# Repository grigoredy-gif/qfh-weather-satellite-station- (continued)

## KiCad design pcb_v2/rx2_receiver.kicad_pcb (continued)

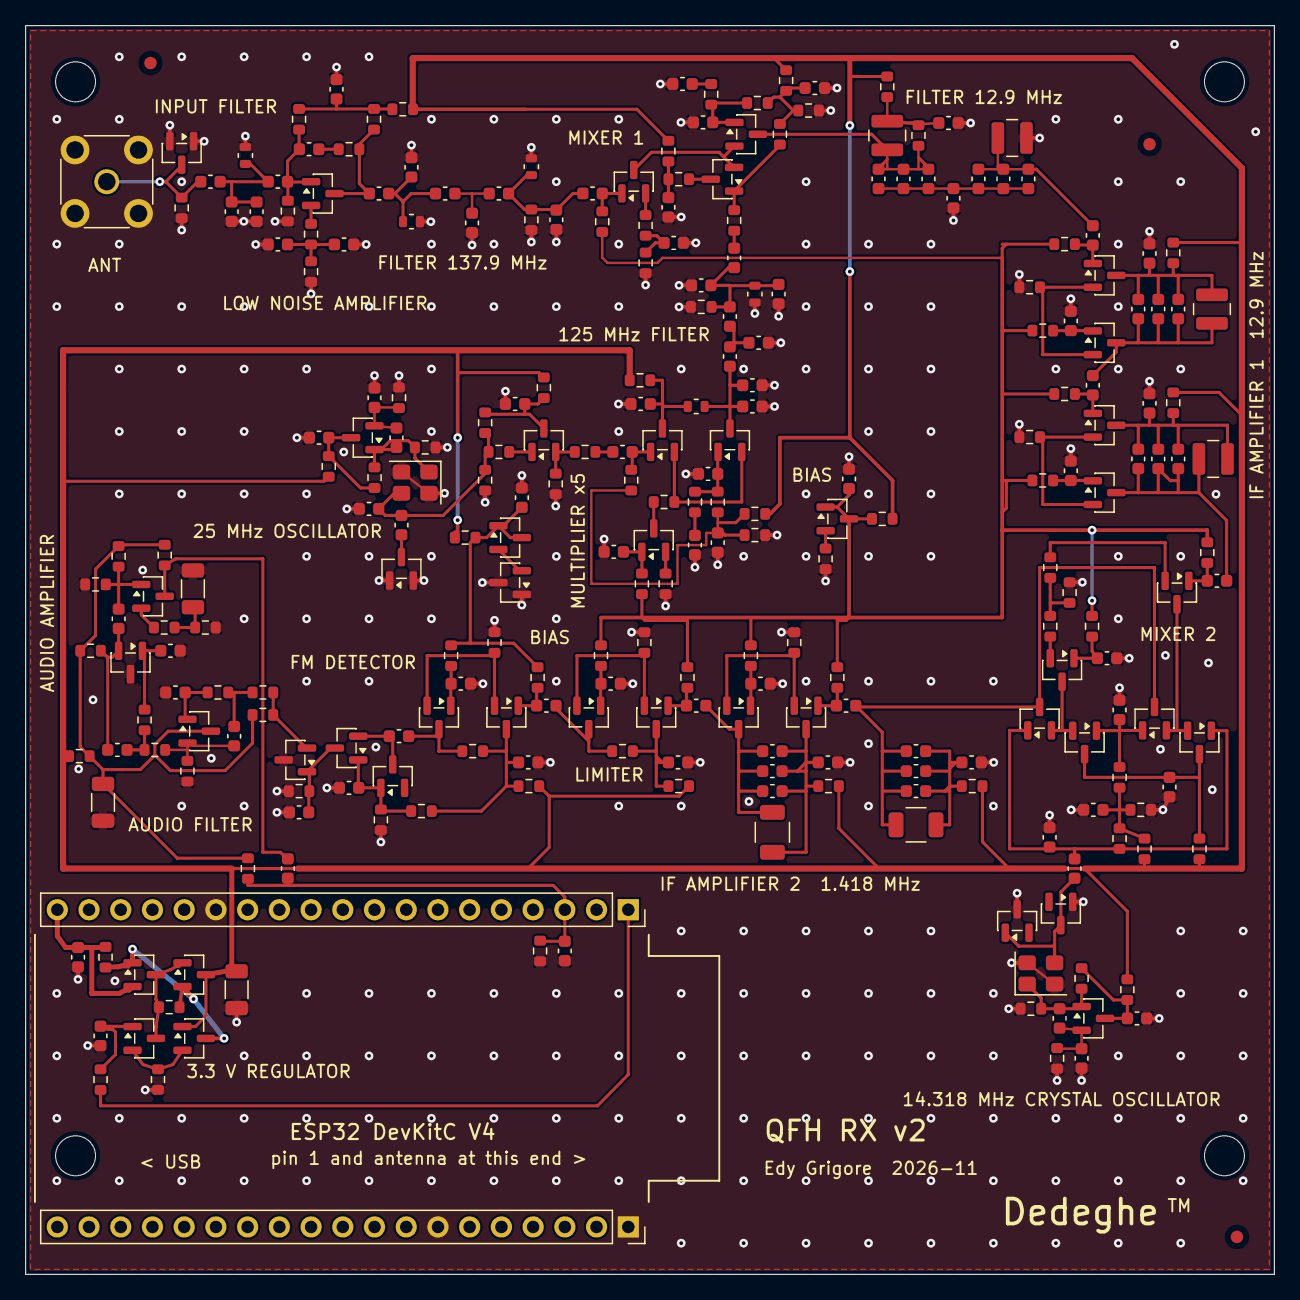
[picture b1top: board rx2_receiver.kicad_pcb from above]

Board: 2 copper layers, 100.0 x 100.0 mm, 273 parts (0 on the bottom side), 117 nets.

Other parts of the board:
FID1, FID2, FID3: Fiducial_1mm_Mask2mm
H1, H2, H3, H4: M3 hole; MountingHole_3.2mm_M3

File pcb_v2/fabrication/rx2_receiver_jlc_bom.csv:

Comment,Designator,Footprint,LCSC Part #
8.2pF,C101,C_0603_1608Metric,C1685
6pF,C102,C_0603_1608Metric,C37474
6.8pF,"C103,C108,C308,C311,C502,C510,C807",C_0603_1608Metric,C1679
1nF,"C104,C105,C106,C304,C402,C404,C405,C507,C512,C701,C804,C809,C903,C905,C909",C_0603_1608Metric,C1588
100nF,"C107,C201,C301,C303,C306,C312,C403,C407,C503,C511,C516,C601,C703,C705,C803,C808,C811,C814",C_0603_1608Metric,C14663
12pF,C109,C_0603_1608Metric,C38523
330pF,"C110,C504",C_0603_1608Metric,C1664
18pF,"C111,C307",C_0603_1608Metric,C1647
47pF,"C202,C501,C505,C816",C_0603_1608Metric,C1671
100pF,"C203,C309,C401,C406,C603,C801,C806",C_0603_1608Metric,C14858
10pF,C204,C_0603_1608Metric,C1634
10nF,"C205,C302,C305,C508,C513,C702,C704,C805,C810,C812,C813",C_0603_1608Metric,C57112
15pF,C310,C_0603_1608Metric,C1644
4.7pF,"C506,C802",C_0603_1608Metric,C1669
33pF,"C509,C514,C605",C_0603_1608Metric,C1663
3pF,C515,C_0603_1608Metric,C46219
68pF,"C602,C604",C_0603_1608Metric,C28262
1uF,"C815,C906,C908",C_0603_1608Metric,C15849
470pF,C817,C_0603_1608Metric,C1620
100uF,"C901,C907,C1003",C_1206_3216Metric,C15008
4.7nF,"C902,C904",C_0603_1608Metric,C53987
10uF,"C1001,C1002,C1101,C1102",C_0603_1608Metric,C19702
BAV99,"D101,D201",SOT-23,C2500
BAS70,"D601,D602,D801",SOT-23,C7502686
68nH,"L101,L102,L103,L301,L302",L_0603_LQW18A,C86135
3.3uH,"L501,L502,L503,L504",L_1008_AHW2520C,C6364740
100uH,"L801,L802",L_1210_NLV32,C295124
2SC3356,"Q101,Q302,Q303,Q304,Q401,Q402,Q403",SOT-23,C28646266
S9018,"Q201,Q301,Q501,Q502,Q503,Q504",SOT-23,C41375130
MMBT3904,"Q601,Q701,Q702,Q703,Q704,Q705,Q706,Q801,Q802,Q803,Q804,Q805,Q806,Q902,Q904,Q1003,Q1004,Q1101,Q1102",SOT-23,C20526
MMBT3906,"Q807,Q901,Q903,Q1001,Q1002,Q1103",SOT-23,C7420354
10k,"R101,R401,R404,R406,R407,R501,R503,R504,R507,R508,R701,R702,R706,R708,R709,R802,R803,R806,R807,R811,R902",R_0603_1608Metric,C25804
1.8k,"R102,R809",R_0603_1608Metric,C4177
1k,"R103,R705",R_0603_1608Metric,C21190
2.2R,R104,R_0603_1608Metric,C22939
33R,"R105,R306",R_0603_1608Metric,C23140
120R,R106,R_0603_1608Metric,C22787
470R,"R107,R204,R812",R_0603_1608Metric,C23179
10R,"R108,R1001",R_0603_1608Metric,C22859
2.2k,"R109,R307,R908,R1004",R_0603_1608Metric,C4190
100R,"R201,R304,R312,R402,R410,R502,R506,R510,R601,R703,R704,R710,R801,R805,R810,R901",R_0603_1608Metric,C22775
22k,"R202,R203,R602,R603,R910",R_0603_1608Metric,C31850
22R,"R301,R316",R_0603_1608Metric,C23345
15k,"R302,R405,R707,R903,R906",R_0603_1608Metric,C22809
33k,R303,R_0603_1608Metric,C4216
390R,"R305,R813",R_0603_1608Metric,C23151
4.7k,"R308,R1103",R_0603_1608Metric,C23162
680R,"R309,R310,R315,R604",R_0603_1608Metric,C23228
47R,"R311,R313,R314,R408,R409,R411,R815,R912",R_0603_1608Metric,C23182
200R,R403,R_0603_1608Metric,C8218
1.2k,"R505,R509,R1003",R_0603_1608Metric,C22765
1.1k,"R804,R814,R1101",R_0603_1608Metric,C22764
560R,R808,R_0603_1608Metric,C23204
1.5k,"R816,R913,R1002",R_0603_1608Metric,C22843
3k,"R817,R911",R_0603_1608Metric,C4211
27k,"R818,R909",R_0603_1608Metric,C22967
5.6k,"R904,R907",R_0603_1608Metric,C23189
2.7k,R905,R_0603_1608Metric,C13167
82k,R914,R_0603_1608Metric,C23254
51k,R915,R_0603_1608Metric,C23196
270R,R1102,R_0603_1608Metric,C22966
25MHz,Y201,Crystal_SMD_3225-4Pin_3.2x2.5mm,C9006
14.31818MHz,Y601,Crystal_SMD_3225-4Pin_3.2x2.5mm,C34748

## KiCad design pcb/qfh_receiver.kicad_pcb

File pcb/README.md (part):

# PCB — discrete 137.9 MHz FM satellite receiver

This is the circuit board for the receiver I simulated in
[`../fm_receiver`](../fm_receiver). The board is built from that simulation:
its schematic was generated from the full-receiver netlist `sim12`, and if the
board and that netlist ever disagree, the netlist wins.

> **Status (November 2026): finished as a design, never ordered or built.**
> The last copper change was on 7 November 2026, and a final check on
> 10 November found nothing that stops the board from working. I did not
> order it: having two boards assembled was quoted at about €140, and by hand
> it means winding 11 coils and aligning 11 trimmers. Its successor,
> [version 2](../pcb_v2), is designed so that JLCPCB can assemble all of it; it
> was ordered on 16 November 2026.
> The comparison is in [the main README](../README.md#from-version-1-to-version-2).

*3D picture of the version 1 board, made by KiCad from the board file (not a photo).*

## The board at a glance

| | |
|---|---|
| Size | 210 × 75 mm, 2 layers, FR4 1.6 mm |
| Parts | 205, all on the top side, all SMD except the 11 hand-wound coils, the antenna SMA, the test SMA and the two ESP32 socket strips |
| Assembly | planned by hand: bare boards from JLCPCB, parts from LCSC (JLC assembly was quoted at about €140 for two boards). Not ordered |
| Bottom layer | one ground plane |
| Controller | ESP32-DevKitC V4 on a socket (its ADC digitizes the audio) |
| Supply | the DevKitC's 5V pin (really about 4.6 V), about 41 mA |
| Checks | KiCad DRC clean at a 0.254 mm clearance floor; schematic and board match pad for pad |

*The final version 1 board from above (KiCad 3D picture). The two yellow strips
across the IF strip are the exposed ground lands for the shield fences.*

*The same board on 13 September 2026 (KiCad 3D picture), before the
through-hole transistors, trimmers and capacitors were swapped for SMD
versions so that a factory could place them. The board was 180 mm long then.*

## Floorplan

```
+----------------------------------------------------------------------------------+
| [SMA ant] BPF (2 air coils, | LNA | MIXER | == IF STRIP, 96 dB, straight ======= |
|  plane cutouts) [SMA test]  | SMD | +L7   |  L1 [1] #F1# [2][3] #F2# [4] lim DET |
|-------- via wall ------------------------------------------------------ via wall|
| LO CHAIN: xtal 25MHz | buffer | x5 (2 air coils) -> up into mixer LO port        |
|                      AUDIO chain (2400 Hz, folds freely) <- from detector        |
|                                   supply filter   ESP32 socket [USB over edge] > |
+----------------------------------------------------------------------------------+
#F1#, #F2# = shield fences: exposed ground strips for 15 mm tin-plate walls
L7, L1 = the two toroid tanks of the IF filter; [1]-[4] = the four IF stages
```

The 4.6 V supply comes in from the ESP32 socket at the right-hand end and is
filtered there before it runs left along the board.

The weakest signals (microvolts) start at the left edge and the strongest
(volts) end at the right. The IF strip runs in a straight line with its input
and output at opposite ends, because with 96 dB of gain even a little coupling
from the output back to the input would make it oscillate.

## Layout rules I followed

- **The bottom layer is ground.** Everything is routed on top, except where a
  trace had to cross another: 27 bottom-layer segments, 171 mm in total on 12
  nets. The longest are two `vb2` bias runs (25 and 16 mm) under the IF strip.
  They carry DC and are bypassed at both ends. Each hop is listed and
  justified in the design log.
- **Shielding provisions for free.** Rows of ground vias between the IF stages
  and between the RF and the LO/audio sections, with exposed ground strips so a
  brass shield can be soldered on later if the strip oscillates.
- **Two shield fences across the toroid row.** A stability study (below)
  showed that the real risk is the toroids themselves, which stand on edge in
  one open row. So the board was made 30 mm longer: a 20 mm gap between
  stage 1 and stage 2 and a 10 mm gap between stage 3 and stage 4. Each gap
  has an exposed ground strip with 15 stitching vias, from the top edge down
  to the via wall. A 15 mm tall tin-plate fence soldered onto each one
  separates three groups:
  - the IF filter and stage 1;
  - stages 2–3;
  - stage 4, the limiter and the detector.

  The strongest sources of feedback (stage 4 and the detector) now have to get
  past two fences to reach the IF filter.
- **Tight RF loops.** Every tuned circuit's parts sit right at its coil, and the
  LNA's emitter bypass is within about 5 mm of copper of the transistor. At VHF
  a few nanohenries of track change the tuning and the gain.
- **A real 50 ohm antenna input.** The SMA feeds the filter through a 1.5 mm
  coplanar line with ground on both sides.
- **Decoupling everywhere.** Every IF stage has its own 100 nF capacitors on its
  supply and on its cascode bias, fed through its own 47 ohm resistor, so the
  stages cannot talk to each other through the supply. The mixer tank L7 has
  its own 10 ohm + 100 nF feed for the same reason.
- **Test points for bring-up.** A second SMA (J2) with a 0 ohm link R65 at the
  filter→LNA seam (remove R65 and J1→J2 is the band-pass filter alone, ready
  for a VNA), an injection pad TP1 at the first IF stage, and a monitor pad
  TP2 on the audio.
- **No parts on the back and no mounting holes**, both on purpose.

The toroids (T37-6, 27 turns) and the air coils (5 mm diameter) use my own
footprints in `qfh_receiver.pretty`. The air-coil footprint keeps copper away
from under the coil, because a ground plane there would kill its Q.

**Winding rule for the toroids: return-wind them.** A winding that advances once
around the core also behaves like one big single turn, and that turn leaks a
magnetic field (the "one-turn effect"). After the last turn, lay the wire back
around the outside of the core to where the winding started, and only then go
to the pin. That cancels most of the leak. It is required on L4, L6 and L5 (the
high-level end of the strip) and costs nothing on the others, so I do it on all
seven.

**Winding rule for the two link windings (L7 and L1): put the 2 turns at the
cold end**, next to pad 1, and ground the link loop with a short wire from L1
pad 5 to L1 pad 1 (about 5 mm). The loop is otherwise floating, and a link
wound over the hot end of a tank has 0.5–1 pF to it. Through the loop that is
0.25–0.5 pF from one tank to the other, next to the 0.77 pF (0.011 × 70 pF)
that the whole designed coupling amounts to. At the cold end and grounded,
that stray path is gone and L13 alone sets the coupling.

**Winding rule for the air coils (L8–L11): spread the turns to a set length.**
Wind them from 0.8 mm wire on a 5 mm former, then pull the turns apart evenly.
The length sets the inductance (Wheeler's formula, good to about ±10 %; a coil
also springs open a little when it comes off the former):

| Coil | Turns | Length | Inductance |
|---|---|---|---|
| L8, L10 (band-pass filter) | 5 | about 7 mm | about 86 nH (82 nH at 7.5 mm) |
| L9, L11 (×5 and LO tanks) | 7 | about 8.2 mm | about 150 nH |

Wound tight, turn against turn, they would be about 120 nH and 190 nH, which
is more than the 4 pF trimmers can pull in. The band-pass coils are a little
short on purpose. Their trimmers are expected near 5 pF of 6 pF: in the
simulation with the board's parasitics, a coil 10 % low needs 6.6 pF, which
the trimmer does not have, and a coil 10 % high needs 4.0 pF, the middle of
its range. At 7 mm the legs also drop straight into the pads.

## How I checked it

KiCad's design-rule check is clean at a 0.254 mm clearance floor. The
schematic was generated from the simulation netlist and compared with the board
pad by pad (436 connections, no differences; the 33 unused ESP32 pins carry
no-connect flags). Every part has a stocked LCSC part number for JLCPCB
assembly. I also had the board reviewed by independent AI review passes, which
is how several of the issues below were found. The last full one, on
6 November 2026, re-ran the simulations against the board as built and checked
it from seven angles (simulation, schematic, RF layout, IF stability, power,
manufacturing, requirements). A final read-only check on 10 November moved no
copper and found nothing that stops the board from working.

## Issues found and fixed

- **Two TO-92 transistor types had base and emitter swapped** because a
  generic symbol used the wrong pin order. Lesson: check each footprint's pinout
  against the datasheet, not against the symbol library.
- **The ESP32 socket would not have powered anything.** The 5 V feed landed on
  a GPIO pin and the enable pin was grounded. I fixed it after checking the
  DevKitC pinout from several sources and every way the module could be
  plugged in.
- **The "5 V" supply is really 4.6 V**, because the DevKitC puts a Schottky
  diode after USB. I re-centred every bias divider in the simulation for 4.6 V
  instead of accepting lower gain.
- **Some specified trimmers did not exist as real parts.** Together with the
  board's own parasitics this pushed three tuned circuits to the end of their
  trimmer range. I re-split the fixed capacitor and the trimmer in each one so
  the trimmer now lands mid-range.
- **The LNA's emitter bypass capacitor was 20 mm from the transistor.** That
  is about 12 nH, which would have cost 4–5 dB of gain. It is now within 5 mm.
- **The IF strip would probably have oscillated.** From the IF filter to the
  last stage there is about 124 dB of gain. In LTspice, a stray coupling of only
  0.045 fF from the last stage back into the IF filter, or a mutual inductance
  of 1.4 pH between two toroids, is enough to make it oscillate. My estimates
  from the board geometry put the toroid-to-toroid coupling at 1–7 times that.
  The supply decoupling and the PCB traces were fine. The fixes are two fences,
  30 mm of extra distance and the return-wound toroids, with the damping
  resistors as a gain knob on the bench. The details are in the design log.
- **Through-hole parts swapped for SMD versions of the same parts** so the board
  can be machine-assembled: the five audio transistors (now MMBT3904/3906 in
  SOT-23), the five diodes, the crystal and the three electrolytics. SOT-23 has
  a different pin order from TO-92 (B-E-C instead of E-B-C), so the schematic
  symbols changed too. I checked afterwards that every pad still carries the
  same net as before.
- **The full check of 6 November 2026 found six more board problems**, all
  fixed:
  - *The IF filter was over-coupled.* Its two toroids are joined by a link
    winding, and the old rule of thumb for the link (k ≈ (n/N)²) is wrong for a
    low-impedance loop. The real coupling would have been 0.08–0.3 instead of
    0.011. That gives one narrow peak, weak skirts and a spurious passband a few
    MHz higher. Fix: 2-turn links plus a 680 nH inductor (L13) in series in the
    link loop. The simulation gives 209 kHz, single-peaked, −24 dB at ±500 kHz.
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
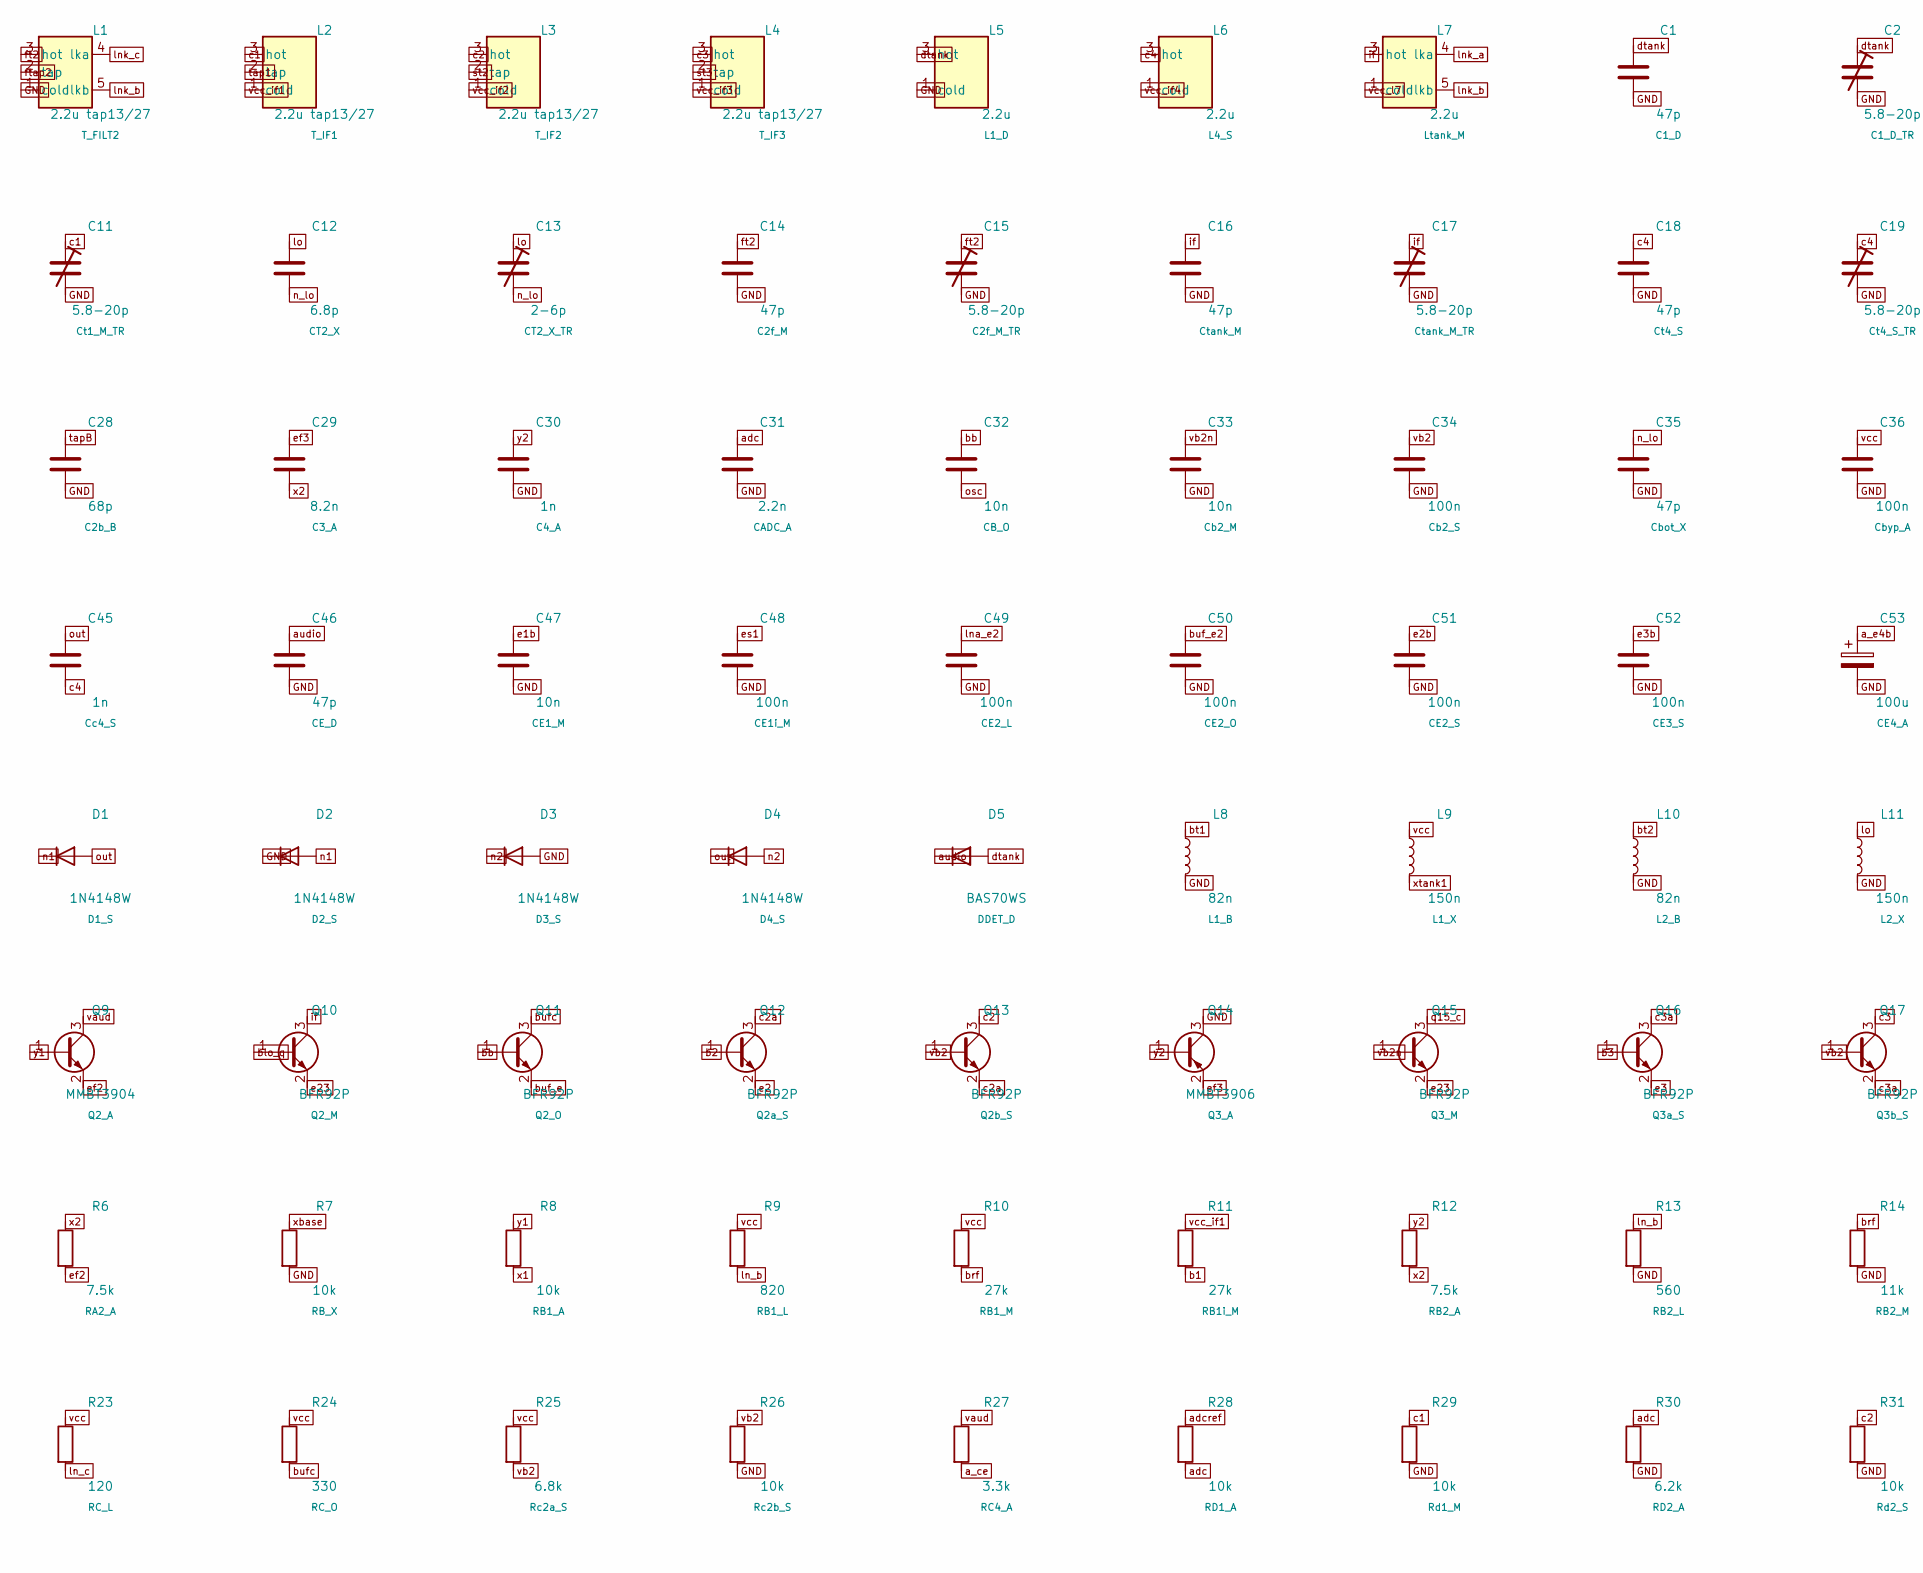
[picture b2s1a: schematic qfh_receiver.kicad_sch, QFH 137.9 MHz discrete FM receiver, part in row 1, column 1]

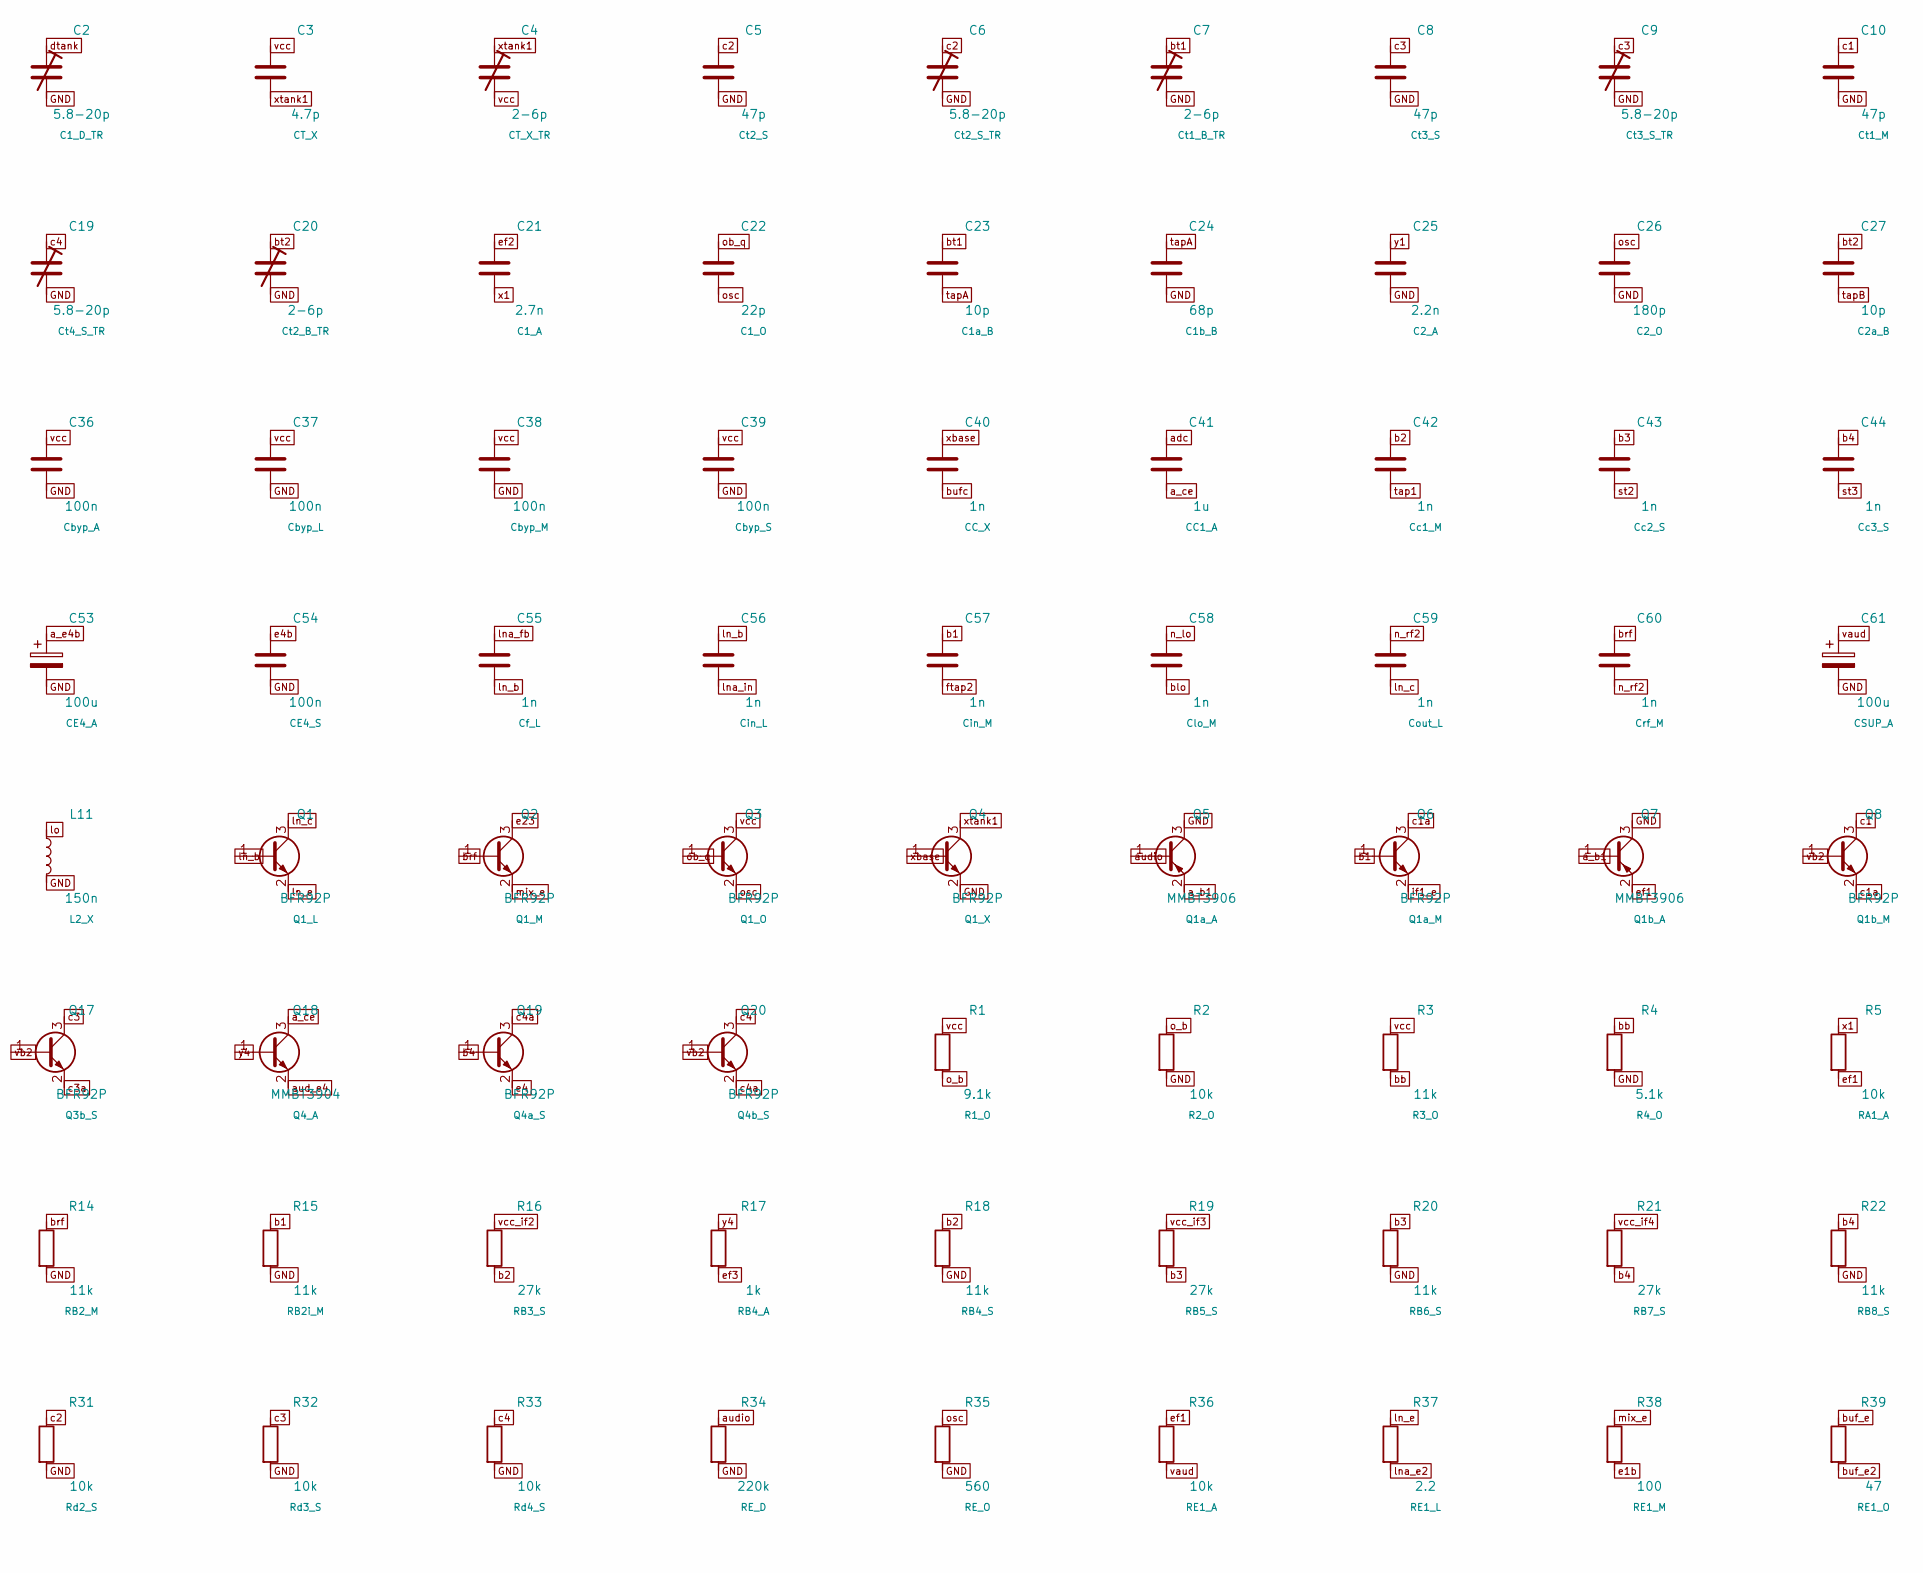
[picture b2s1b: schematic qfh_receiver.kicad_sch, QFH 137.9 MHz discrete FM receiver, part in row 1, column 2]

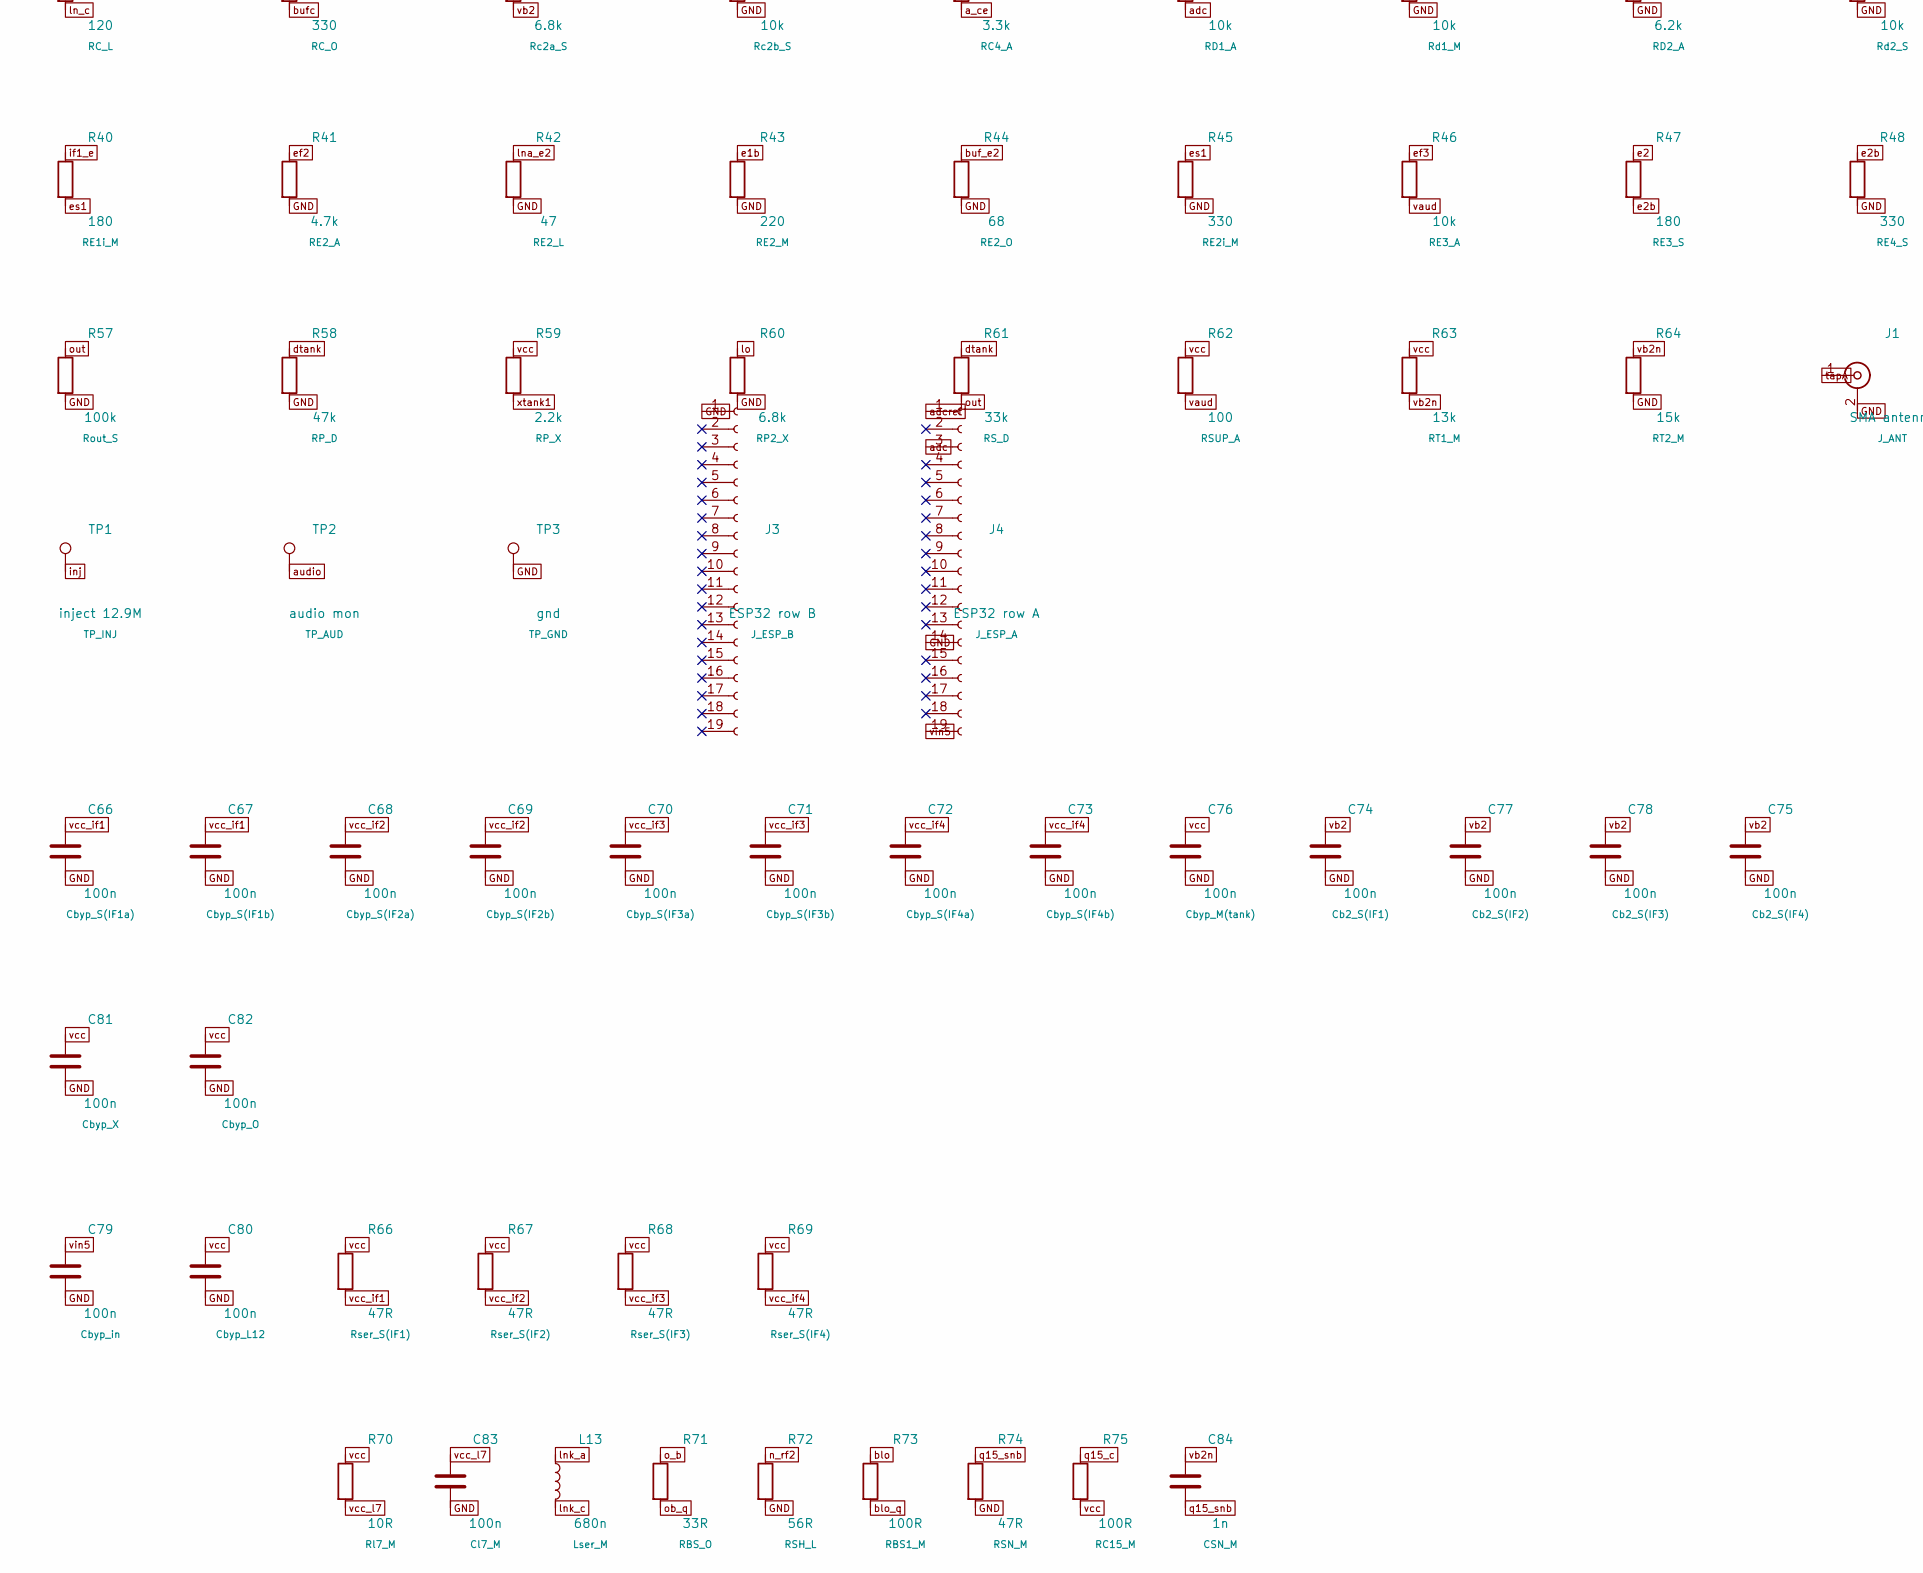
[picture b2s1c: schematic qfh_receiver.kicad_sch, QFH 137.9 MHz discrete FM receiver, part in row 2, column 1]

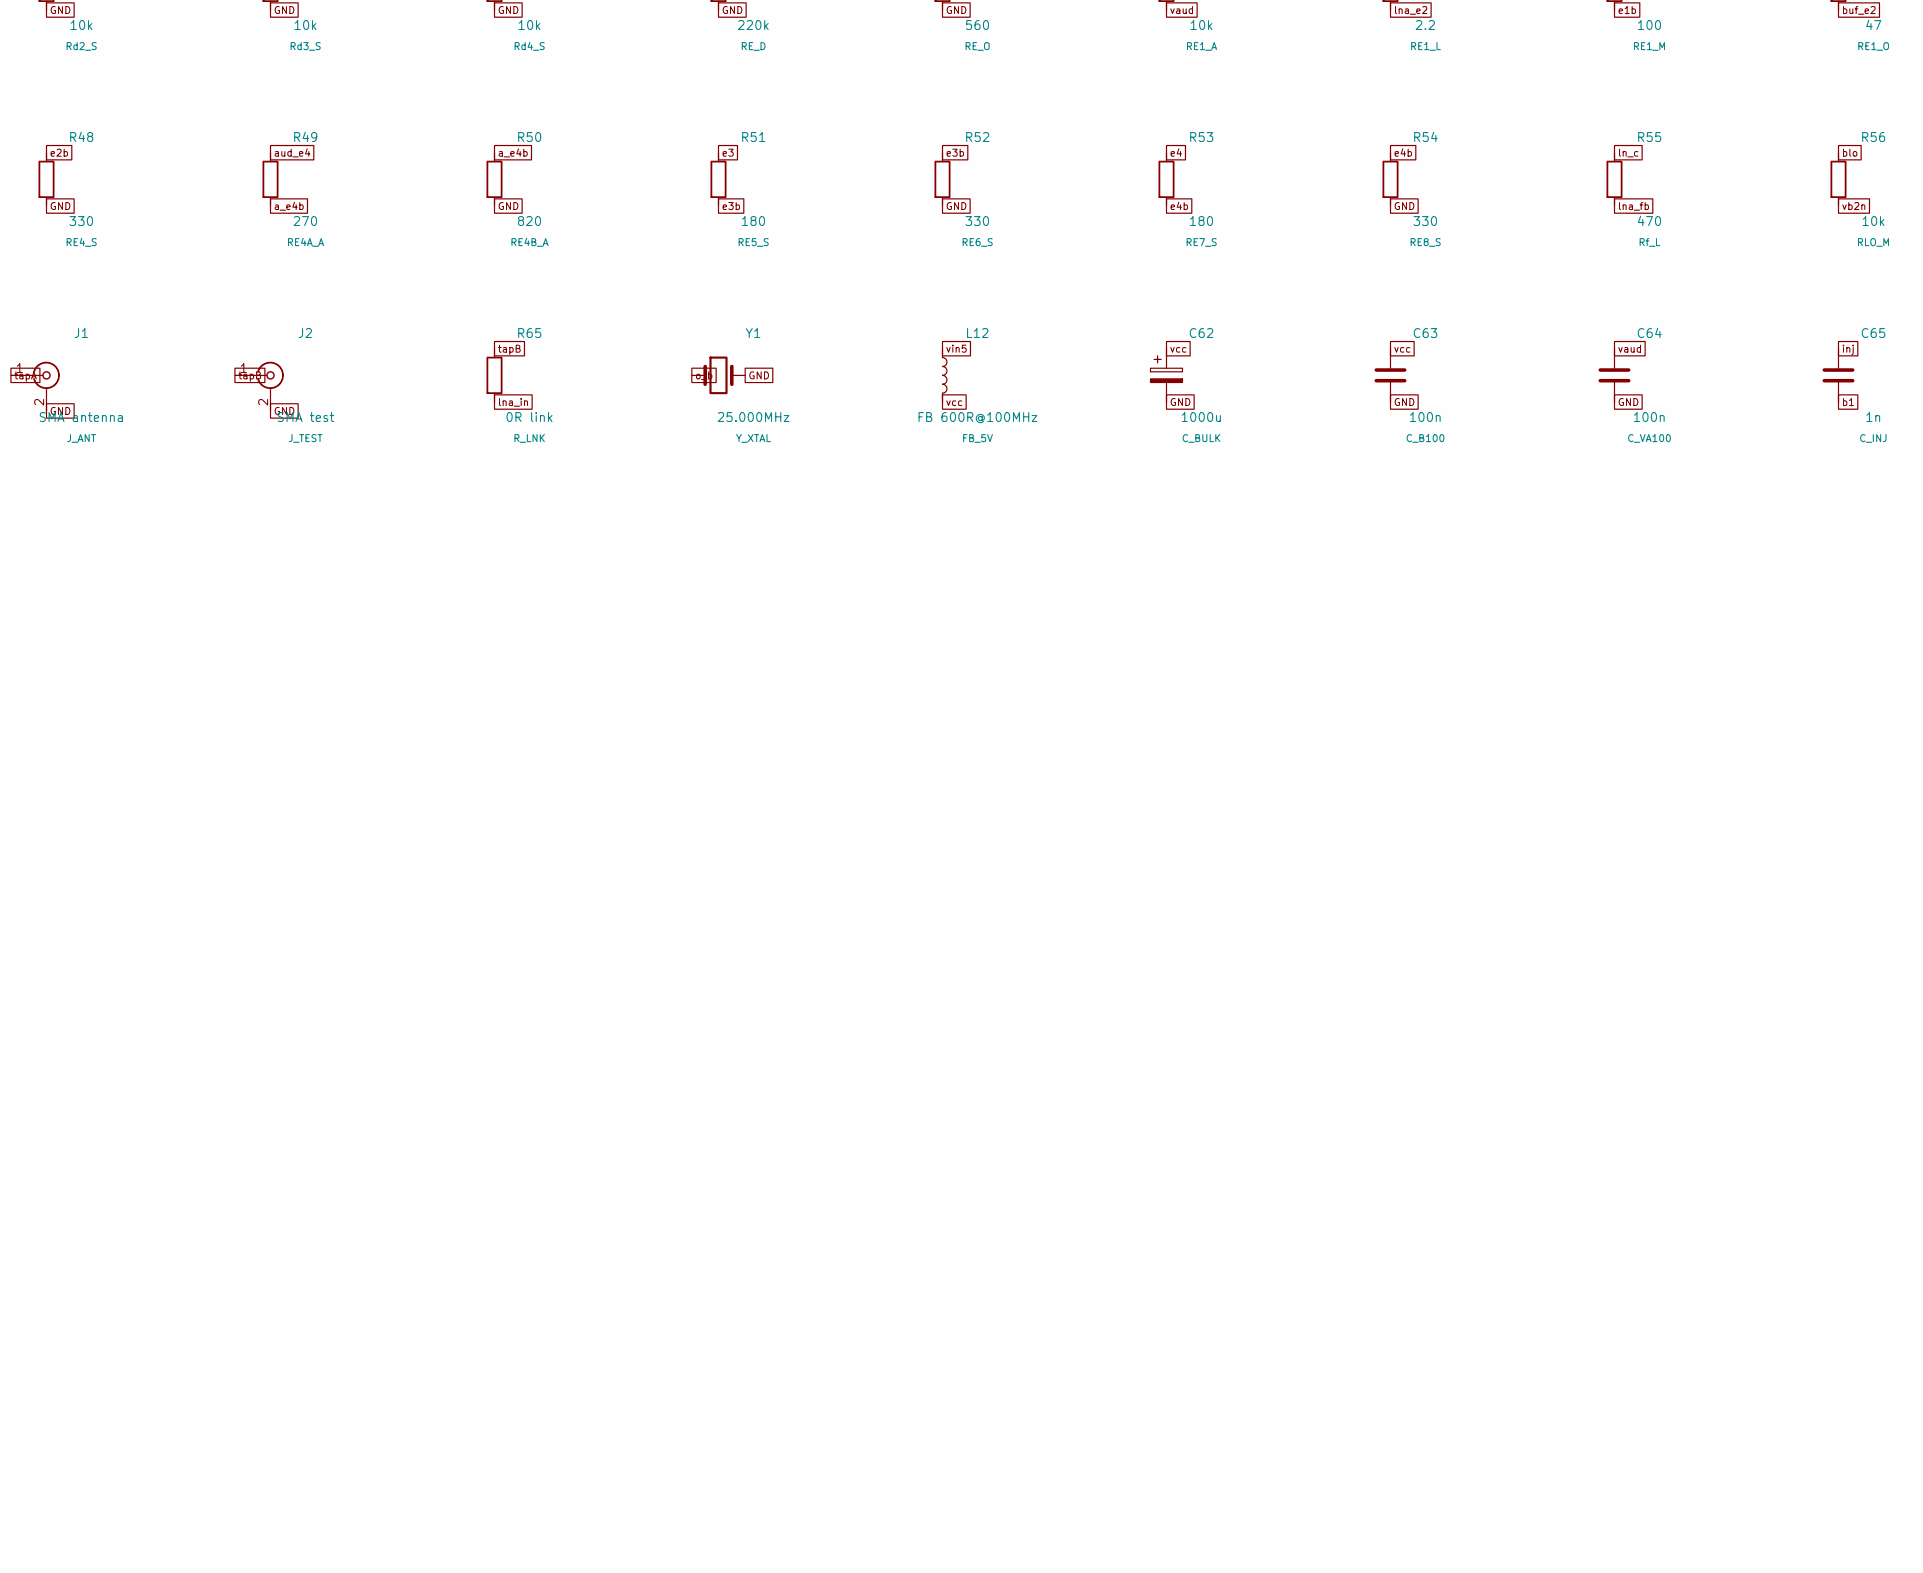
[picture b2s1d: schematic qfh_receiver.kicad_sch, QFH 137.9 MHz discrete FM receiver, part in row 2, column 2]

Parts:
C1, C5, C8, C10, C14, C16, C18, C35, C46: 47p; C_0805_2012Metric; LCSC C14857
C2, C6, C9, C11, C15, C17, C19: 5.8-20p; C_Trimmer_JZ_STC3; MPN STC3MD20-T1; LCSC C22468122
C3: 4.7p; C_0603_1608Metric; LCSC C1669
C4, C7, C13, C20: 2-6p; C_Trimmer_JZ_STC3; MPN STC3MA06-T1; LCSC C22468120
C12: 6.8p; C_0603_1608Metric; LCSC C1679
C21: 2.7n; C_0603_1608Metric; LCSC C1609
C22: 22p; C_0805_2012Metric; LCSC C1804
C23, C27: 10p; C_0603_1608Metric; LCSC C106245
C24, C28: 68p; C_0603_1608Metric; LCSC C28262
C25, C31: 2.2n; C_0805_2012Metric; LCSC C28260
C26: 180p; C_0805_2012Metric; LCSC C527205
C29: 8.2n; C_0603_1608Metric; LCSC C1322360
C30, C40, C42, C43, C44, C45, C55, C56, C57, C58, C59, C60, C65: 1n; C_0805_2012Metric; LCSC C46653
C32, C33, C47: 10n; C_0805_2012Metric; LCSC C1710
C34, C36, C37, C38, C39, C48, C49, C50, C51, C52, C54, C63, C64, C66, C67, C68, C69, C70, C71, C72, C73, C74, C75, C76, C77, C78, C79, C80, C81, C82, C83: 100n; C_0805_2012Metric; LCSC C49678
C41: 1u; C_0805_2012Metric; LCSC C28323
C53, C61: 100u; CP_Elec_6.3x7.7; LCSC C72477
C62: 1000u; CP_Elec_10x10; LCSC C3646816
C84: 1n; C_0603_1608Metric; LCSC C1588
D1, D2, D3, D4: 1N4148W; D_SOD-123; LCSC C81598
D5: BAS70WS; D_SOD-323; LCSC C7502716
J1: SMA antenna; SMA_Amphenol_132289_EdgeMount; MPN 132289; LCSC C496551
J2: SMA test; SMA_BAT_Wireless_BWSMA-KWE-Z001; MPN BWSMA-KWE-Z001; LCSC C496551
J3: ESP32 row B; PinSocket_1x19_P2.54mm_Vertical; LCSC C2932678
J4: ESP32 row A; PinSocket_1x19_P2.54mm_Vertical; LCSC C2932678
L1, L2, L3, L4: 2.2u tap13/27; TOROID_T37-6_UNIVERSAL
L5, L6, L7: 2.2u; TOROID_T37-6_UNIVERSAL
L8, L10: 82n; AIRCOIL_5MM
L9, L11: 150n; AIRCOIL_5MM
L12: FB 600R@100MHz; L_0805_2012Metric; LCSC C21519
L13: 680n; L_0805_2012Metric; LCSC C62554
Q1, Q2, Q3, Q4, Q6, Q8, Q10, Q11, Q12, Q13, Q15, Q16, Q17, Q19, Q20: BFR92P; SOT-23; MPN BFR92PE6327HTSA1; LCSC C273250
Q5, Q7, Q14: MMBT3906; SOT-23; LCSC C7420354
Q9, Q18: MMBT3904; SOT-23; LCSC C20526
R1: 9.1k; R_0805_2012Metric; LCSC C17855
R2, R5, R7, R8, R26, R28, R29, R31, R32, R33, R36, R46, R56: 10k; R_0805_2012Metric; LCSC C17414
R3, R14, R15, R18, R20, R22: 11k; R_0805_2012Metric; LCSC C17429
R4: 5.1k; R_0805_2012Metric; LCSC C27834
R6, R12: 7.5k; R_0805_2012Metric; LCSC C17807
R9, R50: 820; R_0805_2012Metric; LCSC C17837
R10, R11, R16, R19, R21: 27k; R_0805_2012Metric; LCSC C17593
R13, R35: 560; R_0805_2012Metric; LCSC C28636
R17: 1k; R_0805_2012Metric; LCSC C17513
R23: 120; R_0805_2012Metric; LCSC C17437
R24, R45, R48, R52, R54: 330; R_0805_2012Metric; LCSC C17630
R25, R60: 6.8k; R_0805_2012Metric; LCSC C17772
R27: 3.3k; R_0805_2012Metric; LCSC C26010
R30: 6.2k; R_0805_2012Metric; LCSC C17767
R34: 220k; R_0805_2012Metric; LCSC C17556
R37: 2.2; R_0805_2012Metric; LCSC C17521
R38, R62: 100; R_0805_2012Metric; LCSC C17408
R39, R42: 47; R_0805_2012Metric; LCSC C17714
R40, R47, R51, R53: 180; R_0805_2012Metric; LCSC C25270
R41: 4.7k; R_0805_2012Metric; LCSC C17673
R43: 220; R_0805_2012Metric; LCSC C17557
R44: 68; R_0805_2012Metric; LCSC C17802
R49: 270; R_0805_2012Metric; LCSC C17590
R55: 470; R_0805_2012Metric; LCSC C17710
R57: 100k; R_0805_2012Metric; LCSC C149504
R58: 47k; R_0805_2012Metric; LCSC C17713
R59: 2.2k; R_0805_2012Metric; LCSC C17520
R61: 33k; R_0805_2012Metric; LCSC C17633
R63: 13k; R_0805_2012Metric; LCSC C17455
R64: 15k; R_0805_2012Metric; LCSC C17475
R65: 0R link; R_0805_2012Metric; LCSC C17477
R66, R67, R68, R69: 47R; R_0805_2012Metric; LCSC C17714
R70: 10R; R_0805_2012Metric; LCSC C17415
R71: 33R; R_0805_2012Metric; LCSC C17634
R72: 56R; R_0805_2012Metric; LCSC C17757
R73: 100R; R_0805_2012Metric; LCSC C17408
R74: 47R; R_0603_1608Metric; LCSC C23182
R75: 100R; R_0603_1608Metric; LCSC C22775
TP1: inject 12.9M; TestPoint_Pad_D2.0mm
TP2: audio mon; TestPoint_Pad_D2.0mm
TP3: gnd; TestPoint_Pad_D2.0mm
Y1: 25.000MHz; Crystal_SMD_HC49-SD; LCSC C14872

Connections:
GND: C1.2, C2.2, C5.2, C6.2, C7.2, C8.2, C9.2, C10.2, C11.2, C14.2, C15.2, C16.2, C17.2, C18.2, C19.2, C20.2, C24.2, C25.2, C26.2, C28.2, C30.2, C31.2, C33.2, C34.2, C35.2, C36.2, C37.2, C38.2, C39.2, C46.2, C47.2, C48.2, C49.2, C50.2, C51.2, C52.2, C53.2, C54.2, C61.2, C62.2, C63.2, C64.2, C66.2, C67.2, C68.2, C69.2, C70.2, C71.2, C72.2, C73.2, C74.2, C75.2, C76.2, C77.2, C78.2, C79.2, C80.2, C81.2, C82.2, C83.2, D2.1 (K), D3.2 (A), J1.2 (Ext), J2.2 (Ext), J3.1 (Pin_1_1), J4.14, L1.1 (cold), L5.1 (cold), L8.2, L10.2, L11.2, Q4.2 (E), Q5.3 (C), Q7.3 (C), Q14.3 (C), R2.2, R4.2, R7.2, R13.2, R14.2, R15.2, R18.2, R20.2, R22.2, R26.2, R29.2, R30.2, R31.2, R32.2, R33.2, R34.2, R35.2, R41.2, R42.2, R43.2, R44.2, R45.2, R48.2, R50.2, R52.2, R54.2, R57.2, R58.2, R60.2, R64.2, R72.2, R74.2, TP3.1 (1_1), Y1.2
a_b1: Q5.2 (E), Q7.1 (B)
a_ce: C41.2, Q18.3 (C), R27.2
a_e4b: C53.1, R49.2, R50.1
adc: C31.1, C41.1, J4.3, R28.2, R30.1
adcref: J4.1, R28.1
aud_e4: Q18.2 (E), R49.1
audio: C46.1, D5.1 (K), Q5.1 (B), R34.1, TP2.1 (1_1)
b1: C57.1, C65.2, Q6.1 (B), R11.2, R15.1
b2: C42.1, Q12.1 (B), R16.2, R18.1
b3: C43.1, Q16.1 (B), R19.2, R20.1
b4: C44.1, Q19.1 (B), R21.2, R22.1
bb: C32.1, Q11.1 (B), R3.2, R4.1
blo: C58.2, R56.1, R73.1
blo_q: Q10.1 (B), R73.2
brf: C60.1, Q2.1 (B), R10.2, R14.1
bt1: C7.1, C23.1, L8.1
bt2: C20.1, C27.1, L10.1
buf_e: Q11.2 (E), R39.1
buf_e2: C50.1, R39.2, R44.1
bufc: C40.2, Q11.3 (C), R24.2
c1: C10.1, C11.1, L2.3 (hot), Q8.3 (C), R29.1
c1a: Q6.3 (C), Q8.2 (E)
c2: C5.1, C6.1, L3.3 (hot), Q13.3 (C), R31.1
c2a: Q12.3 (C), Q13.2 (E)
c3: C8.1, C9.1, L4.3 (hot), Q17.3 (C), R32.1
c3a: Q16.3 (C), Q17.2 (E)
c4: C18.1, C19.1, C45.2, L6.3 (hot), Q20.3 (C), R33.1
c4a: Q19.3 (C), Q20.2 (E)
dtank: C1.1, C2.1, D5.2 (A), L5.3 (hot), R58.1, R61.1
e1b: C47.1, R38.2, R43.1
e2: Q12.2 (E), R47.1
e2b: C51.1, R47.2, R48.1
e3: Q16.2 (E), R51.1
e3b: C52.1, R51.2, R52.1
e4: Q19.2 (E), R53.1
e4b: C54.1, R53.2, R54.1
e23: Q2.3 (C), Q10.2 (E), Q15.2 (E)
ef1: Q7.2 (E), R5.2, R36.1
ef2: C21.1, Q9.2 (E), R6.2, R41.1
ef3: C29.1, Q14.2 (E), R17.2, R46.1
es1: C48.1, R40.2, R45.1
ft2: C14.1, C15.1, L1.3 (hot)
ftap2: C57.2, L1.2 (tap)
if: C16.1, C17.1, L7.3 (hot), Q10.3 (C)
if1_e: Q6.2 (E), R40.1
inj: C65.1, TP1.1 (1_1)
ln_b: C55.2, C56.1, Q1.1 (B), R9.2, R13.1
ln_c: C59.2, Q1.3 (C), R23.2, R55.1
ln_e: Q1.2 (E), R37.1
lna_e2: C49.1, R37.2, R42.1
lna_fb: C55.1, R55.2
lna_in: C56.2, R65.2
lnk_a: L7.4 (lka), L13.1
lnk_b: L1.5 (lkb), L7.5 (lkb)
lnk_c: L1.4 (lka), L13.2
lo: C12.1, C13.1, L11.1, R60.1
mix_e: Q2.2 (E), R38.1
n1: D1.1 (K), D2.2 (A)
n2: D3.1 (K), D4.2 (A)
n_lo: C12.2, C13.2, C35.1, C58.1
n_rf2: C59.1, C60.2, R72.1
o_b: R1.2, R2.1, R71.1, Y1.1
ob_q: C22.1, Q3.1 (B), R71.2
osc: C22.2, C26.1, C32.2, Q3.2 (E), R35.1
out: C45.1, D1.2 (A), D4.1 (K), R57.1, R61.2
q15_c: Q15.3 (C), R75.1
q15_snb: C84.2, R74.1
st2: C43.2, L3.2 (tap)
st3: C44.2, L4.2 (tap)
tap1: C42.2, L2.2 (tap)
tapA: C23.2, C24.1, J1.1 (In)
tapB: C27.2, C28.1, J2.1 (In), R65.1
vaud: C61.1, C64.1, Q9.3 (C), R27.1, R36.2, R46.2, R62.2
vb2: C34.1, C74.1, C75.1, C77.1, C78.1, Q8.1 (B), Q13.1 (B), Q17.1 (B), Q20.1 (B), R25.2, R26.1
vb2n: C33.1, C84.1, Q15.1 (B), R56.2, R63.2, R64.1
vcc: C3.1, C4.2, C36.1, C37.1, C38.1, C39.1, C62.1, C63.1, C76.1, C80.1, C81.1, C82.1, L9.1, L12.2, Q3.3 (C), R1.1, R3.1, R9.1, R10.1, R23.1, R24.1, R25.1, R59.1, R62.1, R63.1, R66.1, R67.1, R68.1, R69.1, R70.1, R75.2
vcc_if1: C66.1, C67.1, L2.1 (cold), R11.1, R66.2
vcc_if2: C68.1, C69.1, L3.1 (cold), R16.1, R67.2
vcc_if3: C70.1, C71.1, L4.1 (cold), R19.1, R68.2
vcc_if4: C72.1, C73.1, L6.1 (cold), R21.1, R69.2
vcc_l7: C83.1, L7.1 (cold), R70.2
vin5: C79.1, J4.19, L12.1
x1: C21.2, R5.1, R8.2
x2: C29.2, R6.1, R12.2
xbase: C40.1, Q4.1 (B), R7.1
xtank1: C3.2, C4.1, L9.2, Q4.3 (C), R59.2
y1: C25.1, Q9.1 (B), R8.1
y2: C30.1, Q14.1 (B), R12.1
y4: Q18.1 (B), R17.1
